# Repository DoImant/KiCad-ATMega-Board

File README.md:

# ATMega Board

The usual Arduino boards like the Arduino Uno , Nano, Mini etc. are only conditionally suitable for battery operation.

The current requirement of the built-in LEDs, the USB-UART interface and the quite high quiescent current of the LDO regulator is too high for a longer operation on a battery, even if the microcontroller is in sleep mode.

On the ATMega board only the most necessary components are installed, which are necessary for the operation of a microcontroller. This makes it possible to operate the controller with batteries for a longer time. The screw terminals allow stable and trouble-free connections with external components.

With the help of a jumper the power indicator LED (consumes about 3mA) can be switched on or off as needed. 

## Limitations compared to the usual Arduino boards  

* Programming must be done via the ISP adapter.
* For serial communication an external FTDI adapter is required.
* The analog ports A6 and A7 (e.g. compared to an Arduino Nano) are not available.
* No 3.3V output. But you can use the whole board instead of a 5V LDO with a 3.3V LDO (MCP-1703-3302MB
 or HT7833-1).

## Other technical data

* Usable microcontrollers: ATTiny88, ATmega48A/PA, 88A/PA, 168A/PA, 328/P
* The crystal is exchangeable (depending on the inserted microcontroller max. 20Mhz)
* Supply voltage via JST XH connector or VIN-Pin min. 6V, max. 15V
* Max. 200mA current load (the LDO has a limit of 250mA, the AVR controllers 200mA.)
* Power consumption with an ATMega328P in sleep mode *"SLEEP_MODE_PWR_DOWN"* and disabled ADC < 10µA

## Circuit diagram as PDF file

[Sheet](https://github.com/DoImant/Stuff/blob/main/ATMega-Board/ATMega-Board.pdf)

## The PCB

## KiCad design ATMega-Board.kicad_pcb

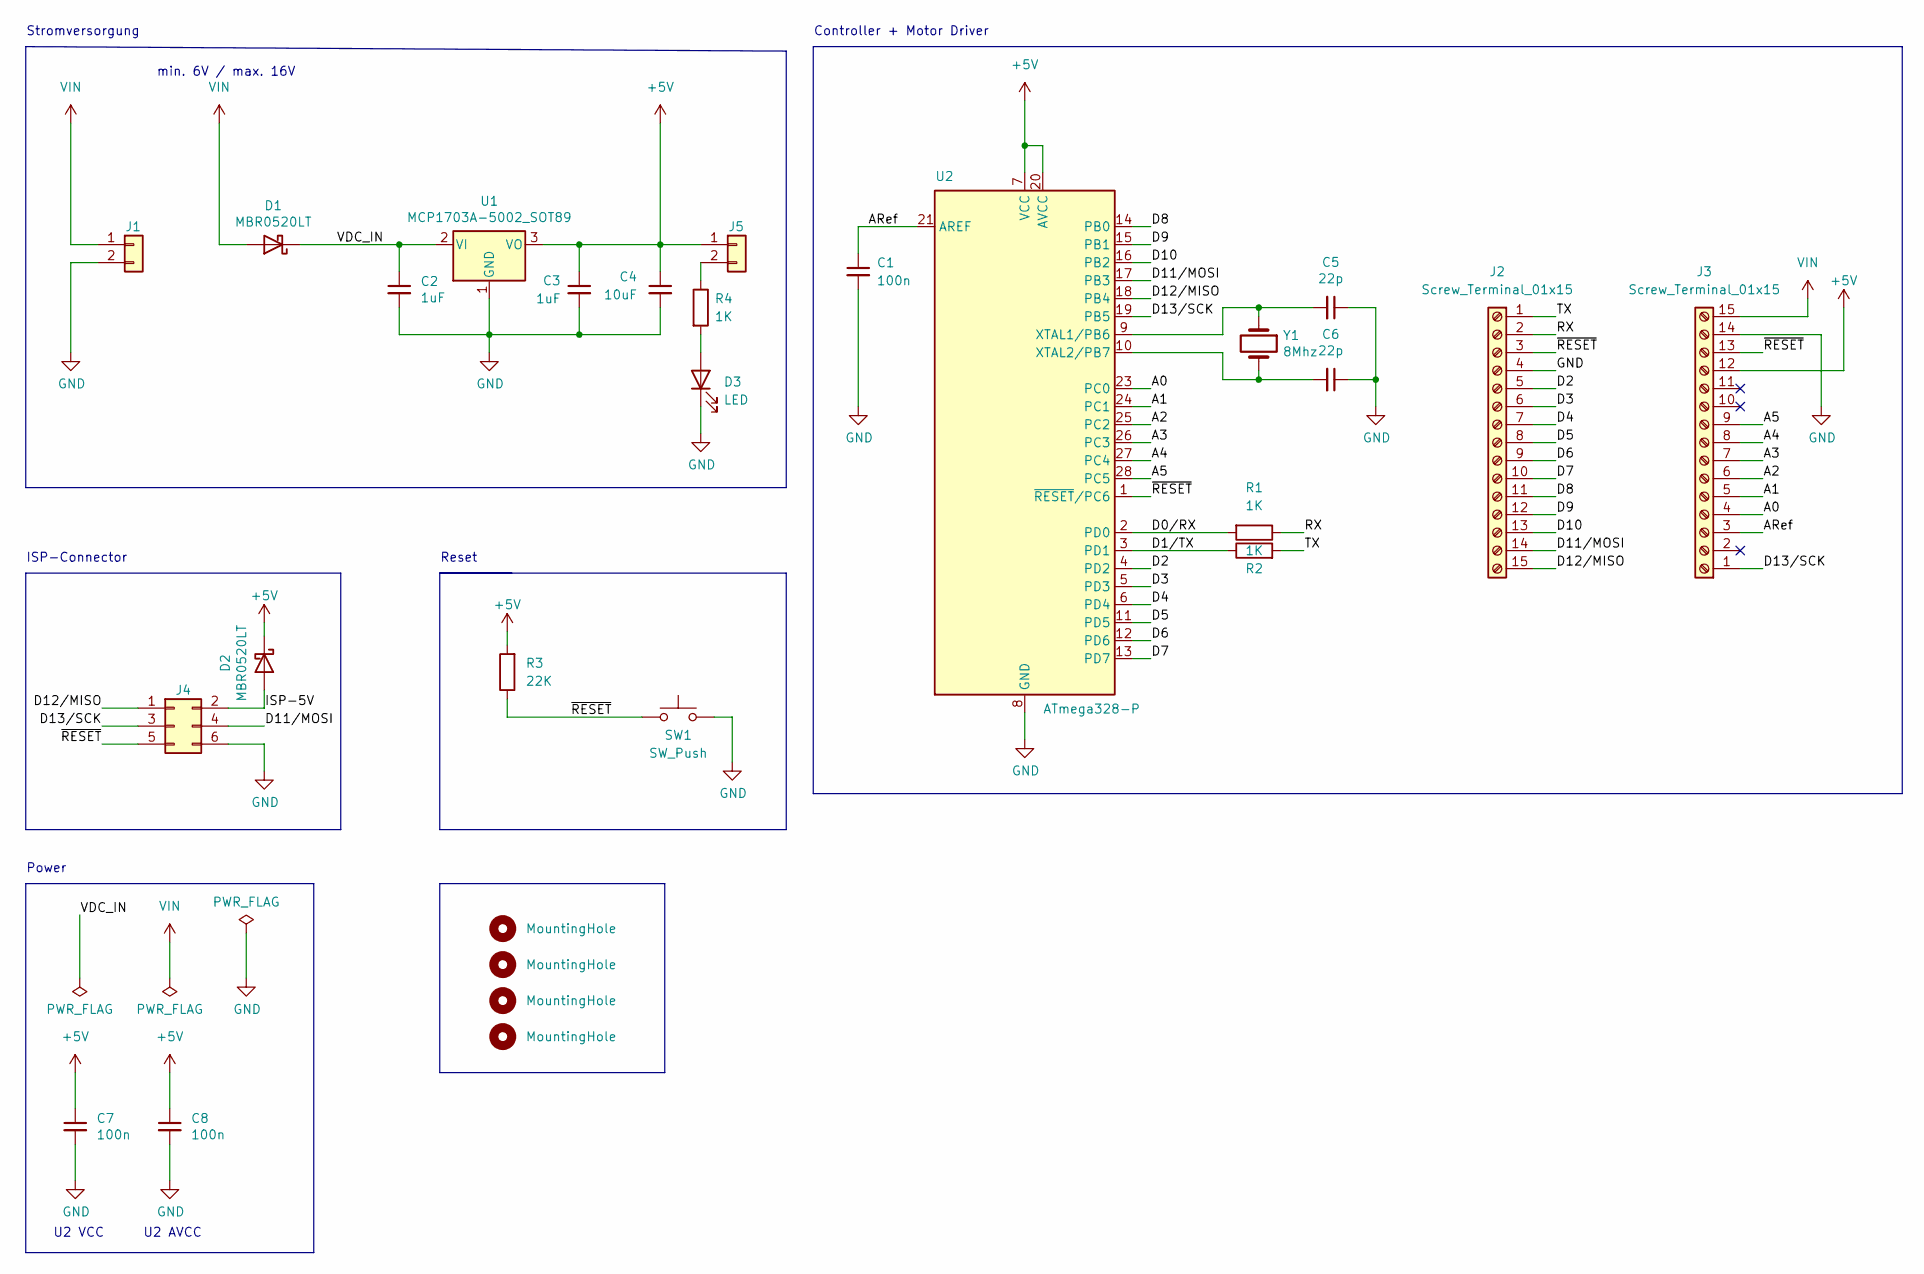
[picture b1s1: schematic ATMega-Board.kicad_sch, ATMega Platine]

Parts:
C1, C7, C8: 100n; C_0805_2012Metric_Pad1.18x1.45mm_HandSolder
C2, C3: 1uF; C_1206_3216Metric_Pad1.33x1.80mm_HandSolder
C4: 10uF; C_1206_3216Metric_Pad1.33x1.80mm_HandSolder
C5, C6: 22p; C_1206_3216Metric_Pad1.33x1.80mm_HandSolder
D1, D2: MBR0520LT; D_SOD-123
D3: LED; LED_1206_3216Metric_Pad1.42x1.75mm_HandSolder
H1, H2, H3, H4: MountingHole; MountingHole_3.2mm_M3_DIN965
J1: Conn_01x02; JST_XH_S2B-XH-A-1_1x02_P2.50mm_Horizontal
J2, J3: Screw_Terminal_01x15; TerminalBlock_Phoenix_PT-1,5-15-5.0-H_1x15_P5.00mm_Horizont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
J4: Conn_02x03_Odd_Even; IDC-Header_2x03_P2.54mm_Vertical
J5: Conn_01x02; PinHeader_1x02_P2.54mm_Vertical
R1, R2, R4: 1K; R_1206_3216Metric_Pad1.30x1.75mm_HandSolder
R3: 22K; R_1206_3216Metric_Pad1.30x1.75mm_HandSolder
SW1: SW_Push; SW_SPST_T931x
U1: MCP1703A-5002_SOT89; SOT-89-3
U2: ATmega328-P; DIP-28_W7.62mm_Socket_LongPads
Y1: 8Mhz; Crystal_HC49-4H_Vertical

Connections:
+5V: C3.1, C4.1, C7.1, C8.1, D2.1 (K), J3.12, J5.1, R3.2, U1.3 (VO), U2.7 (VCC), U2.20 (AVCC)
/A0: J3.4, U2.23 (PC0)
/A1: J3.5, U2.24 (PC1)
/A2: J3.6, U2.25 (PC2)
/A3: J3.7, U2.26 (PC3)
/A4: J3.8, U2.27 (PC4)
/A5: J3.9, U2.28 (PC5)
/ARef: C1.1, J3.3, U2.21 (AREF)
/D0/RX: R1.2, U2.2 (PD0)
/D1/TX: R2.1, U2.3 (PD1)
/D2: J2.5, U2.4 (PD2)
/D3: J2.6, U2.5 (PD3)
/D4: J2.7, U2.6 (PD4)
/D5: J2.8, U2.11 (PD5)
/D6: J2.9, U2.12 (PD6)
/D7: J2.10, U2.13 (PD7)
/D8: J2.11, U2.14 (PB0)
/D9: J2.12, U2.15 (PB1)
/D10: J2.13, U2.16 (PB2)
/D11/MOSI: J2.14, J4.4, U2.17 (PB3)
/D12/MISO: J2.15, J4.1, U2.18 (PB4)
/D13/SCK: J3.1, J4.3, U2.19 (PB5)
/ISP-5V: D2.2 (A), J4.2
/RX: J2.2, R1.1
/TX: J2.1, R2.2
/VDC_IN: C2.1, D1.1 (K), U1.2 (VI)
/~RESET: J2.3, J3.13, J4.5, R3.1, SW1.1, U2.1 (~RESET/PC6)
GND: C1.2, C2.2, C3.2, C4.2, C5.1, C6.1, C7.2, C8.2, D3.1 (K), J1.2, J2.4, J3.14, J4.6, SW1.2, U1.1 (GND), U2.8 (GND), U2.22 (GND); also elsewhere on the board
unnamed: C5.2, U2.9 (XTAL1/PB6), Y1.1
unnamed: C6.2, U2.10 (XTAL2/PB7), Y1.2
unnamed: D3.2 (A), R4.2
unnamed: J5.2, R4.1
VIN: D1.2 (A), J1.1, J3.15; also elsewhere on the board

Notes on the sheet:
Controller + Motor Driver
min. 6V / max. 16V
Power
Stromversorgung
U2 AVCC
ISP-Connector
U2 VCC
Reset

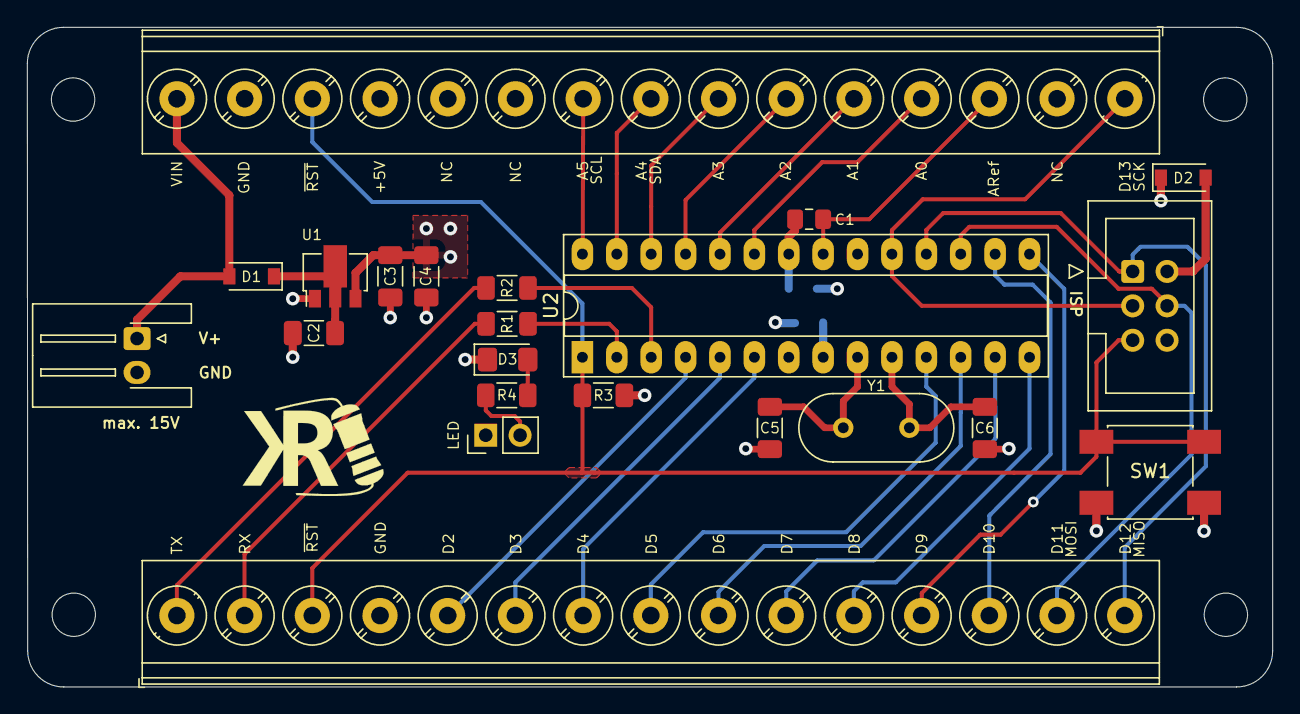
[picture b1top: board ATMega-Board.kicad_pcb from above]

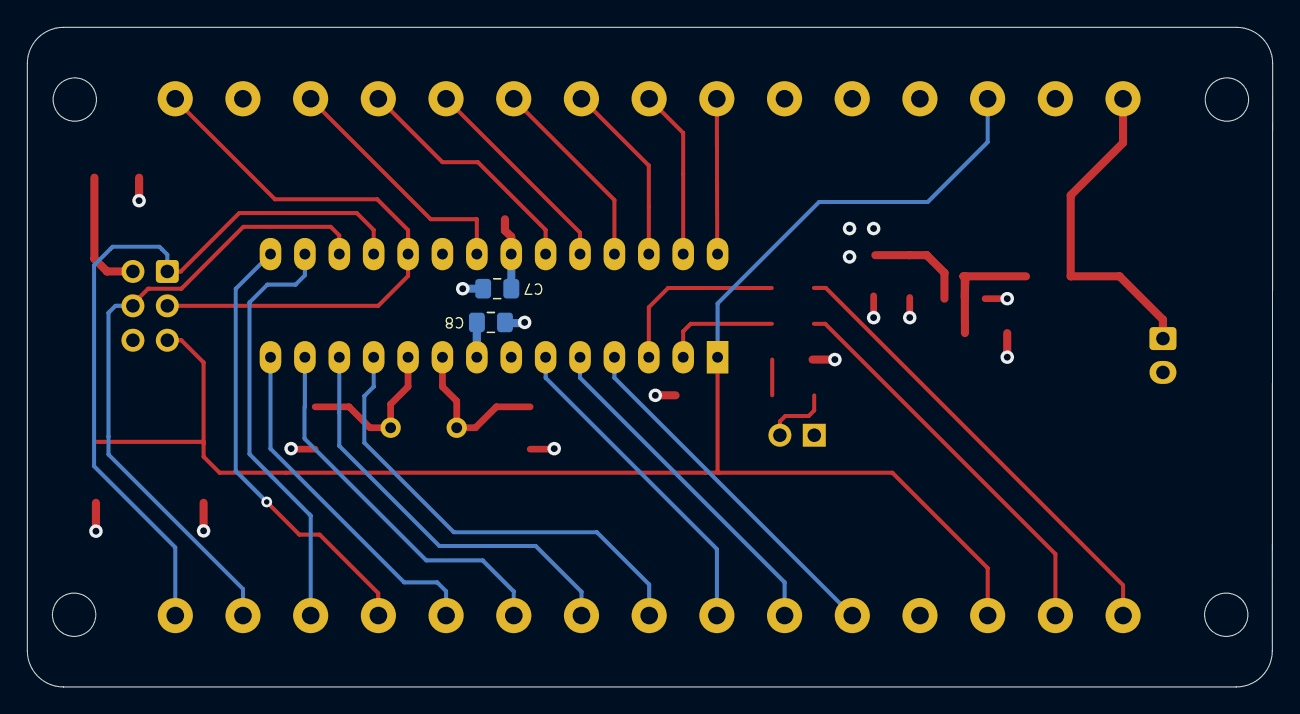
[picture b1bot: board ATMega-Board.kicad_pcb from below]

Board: 4 copper layers, 92.0 x 48.7 mm, 28 parts (2 on the bottom side), 33 nets.

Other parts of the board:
locked: Conn_01x02; JST_XH_S2B-XH-A-1_1x02_P2.50mm_Horizontal

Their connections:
GND: locked.2; also elsewhere on the board
VIN: locked.1; also elsewhere on the board

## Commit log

2022-10-30 README.md supplemented
2022-10-30 Resistor designation adjusted
2022-10-31 Entry supplemented
2022-11-03 Text added
